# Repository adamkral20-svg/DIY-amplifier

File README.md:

# DIY-amplifier
Custom class-d amplifier board.
I made this since i previously tested a smaller version and i love loud music.
The project uses an oscillator design based on the schematic of [SineLab](https://www.youtube.com/@SineLab). I did change a few things to fit my design better.

This board is a Class - D audio amplifier with analog input(3.5mm audio jack) and gain setting.
It can work with 4-16 ohm speaker on output, and supply voltage < 35V. has OCP latch and a glass fuse.

It uses 4 MOSFETS in an H-bridge configuration, allowing for BTL output and thus higher power from lower supply voltage. 
The main part is the HIP-4081A H-bridge MOSFET gate driver. It can reliably drive the MOSFETS in the hundreds of kHz switching speed.

The onboard discrete oscillator should be around 200kHz.
It uses a pnp constant current source connected to a capacitor, and a MOSFET to discharge the capacitor quickly to generate a Ramp wave.
The MOSFET has 0.7nC gate charge, so the TLV3501 can reliably drive it with its output current capability.

The design by Sine lab

The overcurrent protection shuts off all MOSFETS when triggered, and keeps them off until the button is pressed. 
It uses an npn-pnp SCR based design to output a constant signal with a single pulse.

The pwm modulation is made possible by the MCP6561 comparator. 

To keep voltage levels for the audio and ramp wave similar, I'm using a 2V DC bias on audio, since the ramp wave is 0-4V

The logic circuits are powered by 7812 and 7805 repectively. 
I used many caps between VCC and GND to keep noise low from the H-bridge

# PCB layers
It uses 4 layers, since wiring it up with 2 layers, and still handling enough current was impossible, so i changed it to 4 to fit into < 100mm x 100mm size and handle ~5A on the output.

# Layer 1(Vcc)

# Layer 2(5V)

# Layer 3(12V)

# Layer 4(GND)

# Credits

- [KiCad](https://www.kicad.org/)
- [Fusion 360](https://www.autodesk.com/products/fusion-360/overview)
- [Blueprint project](https://blueprint.hackclub.com/projects/10381)

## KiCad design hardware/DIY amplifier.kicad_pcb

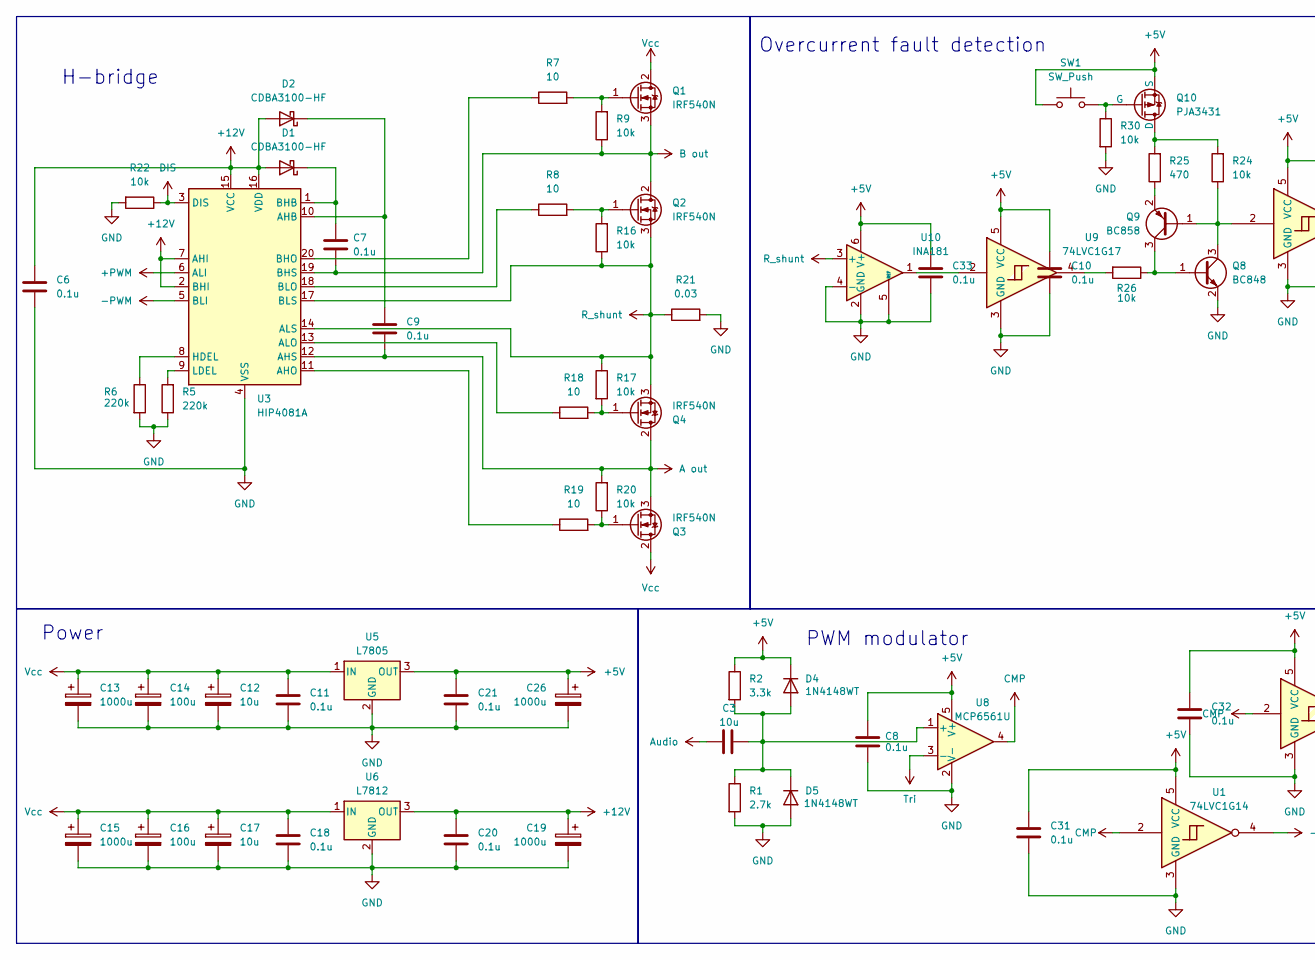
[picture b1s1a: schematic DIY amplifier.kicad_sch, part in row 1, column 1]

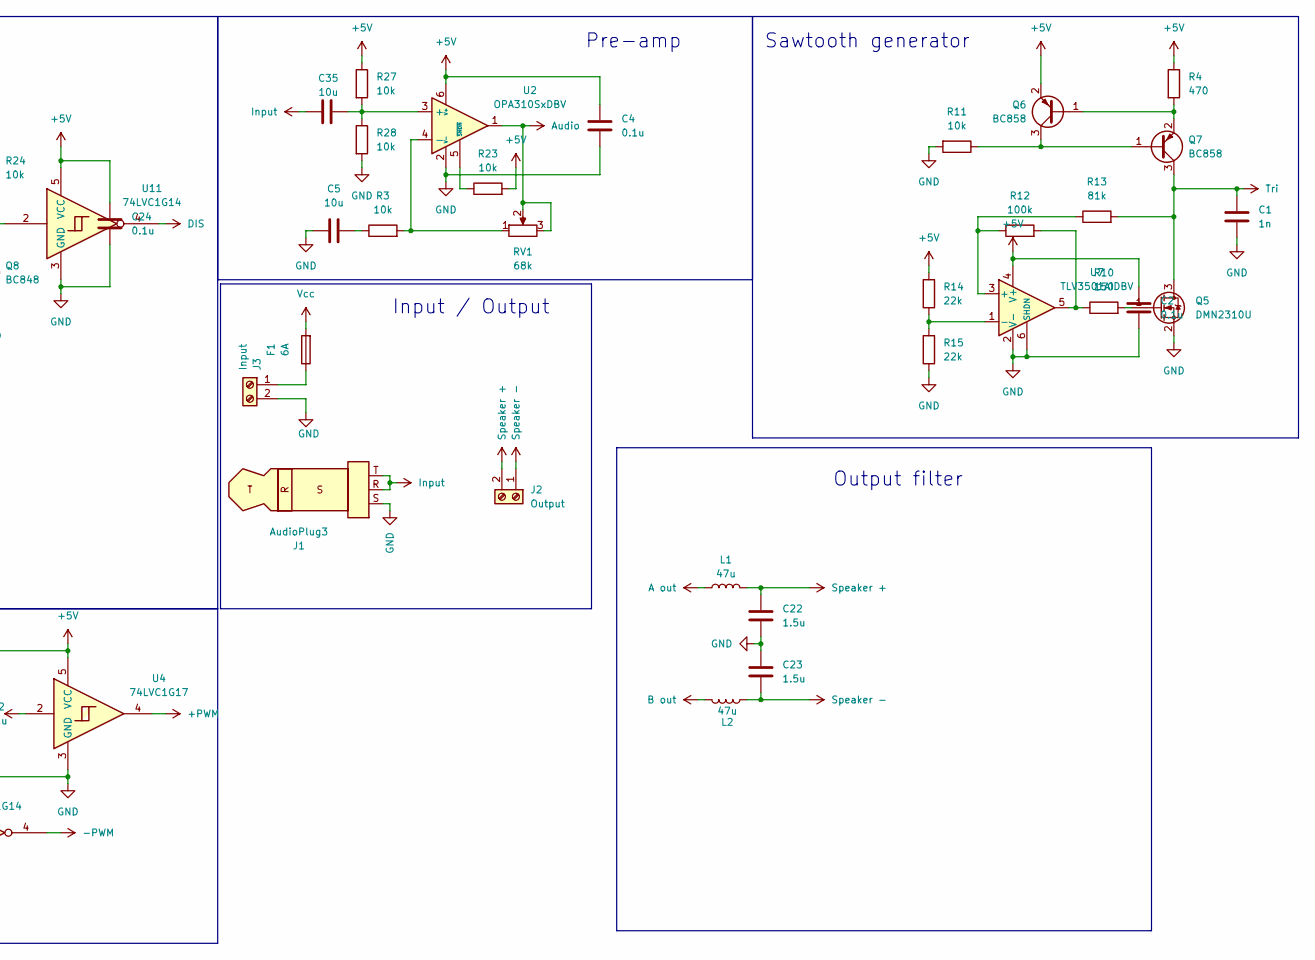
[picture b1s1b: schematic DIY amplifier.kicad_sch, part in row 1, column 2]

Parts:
C1: 1n; C_0402_1005Metric
C2, C4, C6, C7, C8, C9, C10, C24, C31, C32, C33: 0.1u; C_0402_1005Metric
C3, C5, C35: 10u; C_0402_1005Metric
C11, C18, C20, C21: 0.1u; C_Disc_D3.0mm_W1.6mm_P2.50mm
C12, C17: 10u; CP_Radial_D4.0mm_P2.00mm
C13, C15, C19, C26: 1000u; CP_Radial_D12.5mm_P5.00mm
C14, C16: 100u; CP_Radial_D8.0mm_P3.50mm
C22, C23: 1.5u; C_Disc_D3.0mm_W1.6mm_P2.50mm
D1, D2: CDBA3100-HF; D_SMA
D4, D5: 1N4148WT; D_SOD-523
F1: 6A; Fuseholder_Clip-5x20mm_Eaton_1A5601-01_Inline_P20.80x6.76mm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
J1: AudioPlug3; Jack_3.5mm_CUI_SJ-3523-SMT_Horizontal
J2: Output; TerminalBlock_4Ucon_1x02_P3.50mm_Horizontal
J3: Input; TerminalBlock_4Ucon_1x02_P3.50mm_Horizontal
L1, L2: 47u; L_Toroid_Vertical_L14.0mm_W6.3mm_P4.57mm_Pulse_A
Q1, Q2, Q3, Q4: IRF540N; TO-220-3_Horizontal_TabUp
Q5: DMN2310U; SOT-23
Q6, Q7, Q9: BC858; SOT-23
Q8: BC848; SOT-23
Q10: PJA3431; SOT-23-3
R1: 2.7k; R_0603_1608Metric
R2: 3.3k; R_0603_1608Metric
R3, R9, R11, R16, R17, R20, R22, R23, R24, R26, R27, R28, R30: 10k; R_0603_1608Metric
R4, R25: 470; R_0603_1608Metric
R5, R6: 220k; R_0603_1608Metric
R7, R8, R18, R19: 10; R_1206_3216Metric
R10: 150; R_0603_1608Metric
R12: 100k; R_0603_1608Metric
R13: 81k; R_0603_1608Metric
R14, R15: 22k; R_0603_1608Metric
R21: 0.03; R_2512_6332Metric
RV1: 68k; Potentiometer_ACP_CA9-H2,5_Horizontal
SW1: SW_Push; SW_PUSH_6mm_H13mm
U1, U11: 74LVC1G14; SOT-23-5
U2: OPA310SxDBV; SOT-23-6
U3: HIP4081A; DIP-20_W7.62mm
U4, U9: 74LVC1G17; SOT-23-5
U5: L7805; TO-220-3_Vertical
U6: L7812; TO-220-3_Vertical
U7: TLV3501AIDBV; SOT-23-6
U8: MCP6561U; SOT-23-5
U10: INA181; SOT-23-6

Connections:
+5V: C2.1, C4.1, C8.1, C10.1, C21.2, C24.1, C26.1, C31.1, C32.1, C33.1, D4.1 (K), Q6.2 (E), Q10.3 (S), R2.1, R4.1, R14.2, R23.2, R27.1, SW1.1, U1.5 (VCC), U2.6 (V+), U4.5 (VCC), U5.3 (OUT), U7.4 (V+), U8.5 (V+), U9.5 (VCC), U10.6 (V+), U11.5 (VCC)
+12V: C6.1, C19.1, C20.2, D1.2 (A), D2.2 (A), U3.2 (BHI), U3.7 (AHI), U3.15 (VCC), U3.16 (VDD), U6.3 (OUT)
+PWM: U3.6 (ALI), U4.4
-PWM: U1.4, U3.5 (BLI)
A out: C9.2, L1.1, Q3.3 (S), Q4.2 (D), R20.2, U3.12 (AHS)
Audio: C3.1, RV1.2, RV1.3, U2.1
B out: C7.2, L2.1, Q1.3 (S), Q2.2 (D), R9.1, U3.19 (BHS)
CMP: U1.2, U4.2, U8.4
DIS: R22.1, U3.3 (DIS), U11.4
GND: C1.2, C2.2, C4.2, C5.1, C6.2, C8.2, C10.2, C11.1, C12.2, C13.2, C14.2, C15.2, C16.2, C17.2, C18.1, C19.2, C20.1, C21.1, C22.1, C23.1, C24.2, C26.2, C31.2, C32.2, C33.2, D5.2 (A), J1.S, J3.2, Q5.2 (S), Q8.2 (E), R1.2, R5.1, R6.2, R11.2, R15.1, R21.2, R22.2, R28.2, R30.2, U1.3 (GND), U2.2 (V-), U3.4 (VSS), U4.3 (GND), U5.2 (GND), U6.2 (GND), U7.2 (V-), U7.6 (SHDN), U8.2 (V-), U9.3 (GND), U10.2 (GND), U10.4 (-), U10.5 (REF), U11.3 (GND)
Input: C35.1, J1.R, J1.T
unnamed: C5.2, R3.1
unnamed: C7.1, D1.1 (K), U3.1 (BHB)
unnamed: C9.1, D2.1 (K), U3.10 (AHB)
unnamed: C3.2, D4.2 (A), D5.1 (K), R1.1, R2.2, U8.1 (+)
unnamed: F1.1, J3.1
unnamed: Q1.1 (G), R7.2, R9.2
unnamed: Q2.1 (G), R8.2, R16.2
unnamed: Q3.1 (G), R19.2, R20.1
unnamed: Q4.1 (G), R17.2, R18.2
unnamed: Q5.1 (G), R10.2
unnamed: Q6.1 (B), Q7.2 (E), R4.2
unnamed: Q6.3 (C), Q7.1 (B), R11.1
unnamed: Q8.1 (B), Q9.3 (C), R26.1
unnamed: Q8.3 (C), Q9.1 (B), R24.1, U11.2
unnamed: Q9.2 (E), R25.1
unnamed: Q10.1 (D), R24.2, R25.2
unnamed: Q10.2 (G), R30.1, SW1.2
unnamed: R10.1, R12.2, U7.5
unnamed: R26.2, U9.4
unnamed: C35.2, R27.2, R28.1, U2.3 (+)
unnamed: R3.2, RV1.1, U2.4 (-)
unnamed: R23.1, U2.5 (~SHDN)
unnamed: R19.1, U3.11 (AHO)
unnamed: R18.1, U3.13 (ALO)
unnamed: R7.1, U3.20 (BHO)
unnamed: R8.1, U3.18 (BLO)
unnamed: R6.1, U3.8 (HDEL)
unnamed: R5.2, U3.9 (LDEL)
unnamed: R12.1, R13.1, U7.3 (+)
unnamed: R14.1, R15.2, U7.1 (-)
unnamed: U9.2, U10.1
R_shunt: Q2.3 (S), Q4.3 (S), R16.1, R17.1, R21.1, U3.14 (ALS), U3.17 (BLS), U10.3 (+)
Tri: C1.1, Q5.3 (D), Q7.3 (C), R13.2, U8.3 (-)
Vcc: C11.2, C12.1, C13.1, C14.1, C15.1, C16.1, C17.1, C18.2, F1.2, Q1.2 (D), Q3.2 (D), U5.1 (IN), U6.1 (IN)

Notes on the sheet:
H-bridge
Sawtooth generator
Overcurrent fault detection
PWM modulator
Pre-amp
Power
Output filter
Input / Output

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
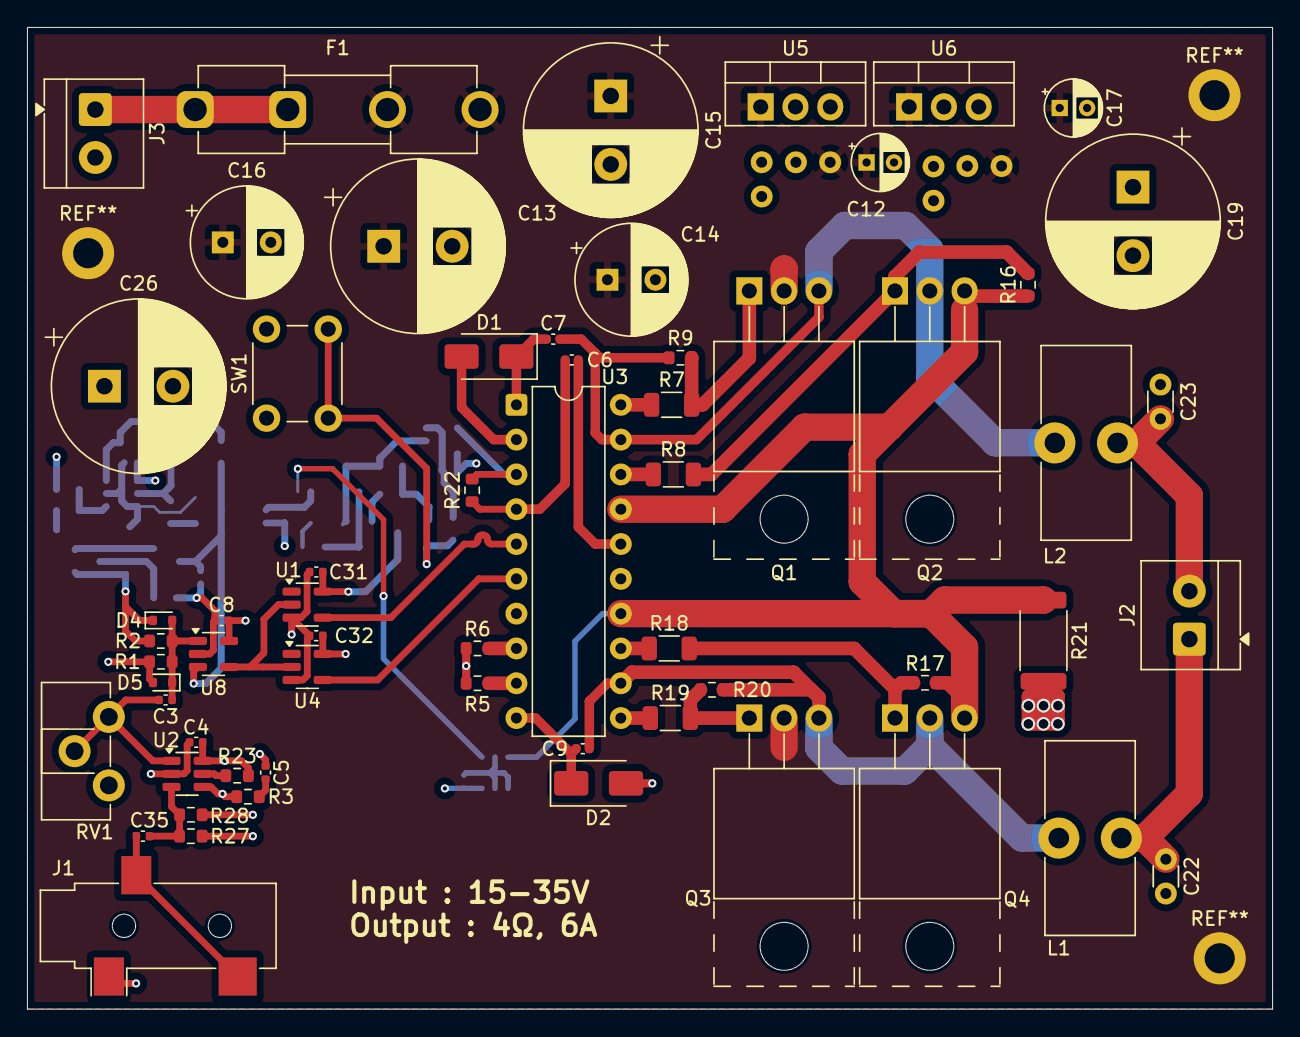
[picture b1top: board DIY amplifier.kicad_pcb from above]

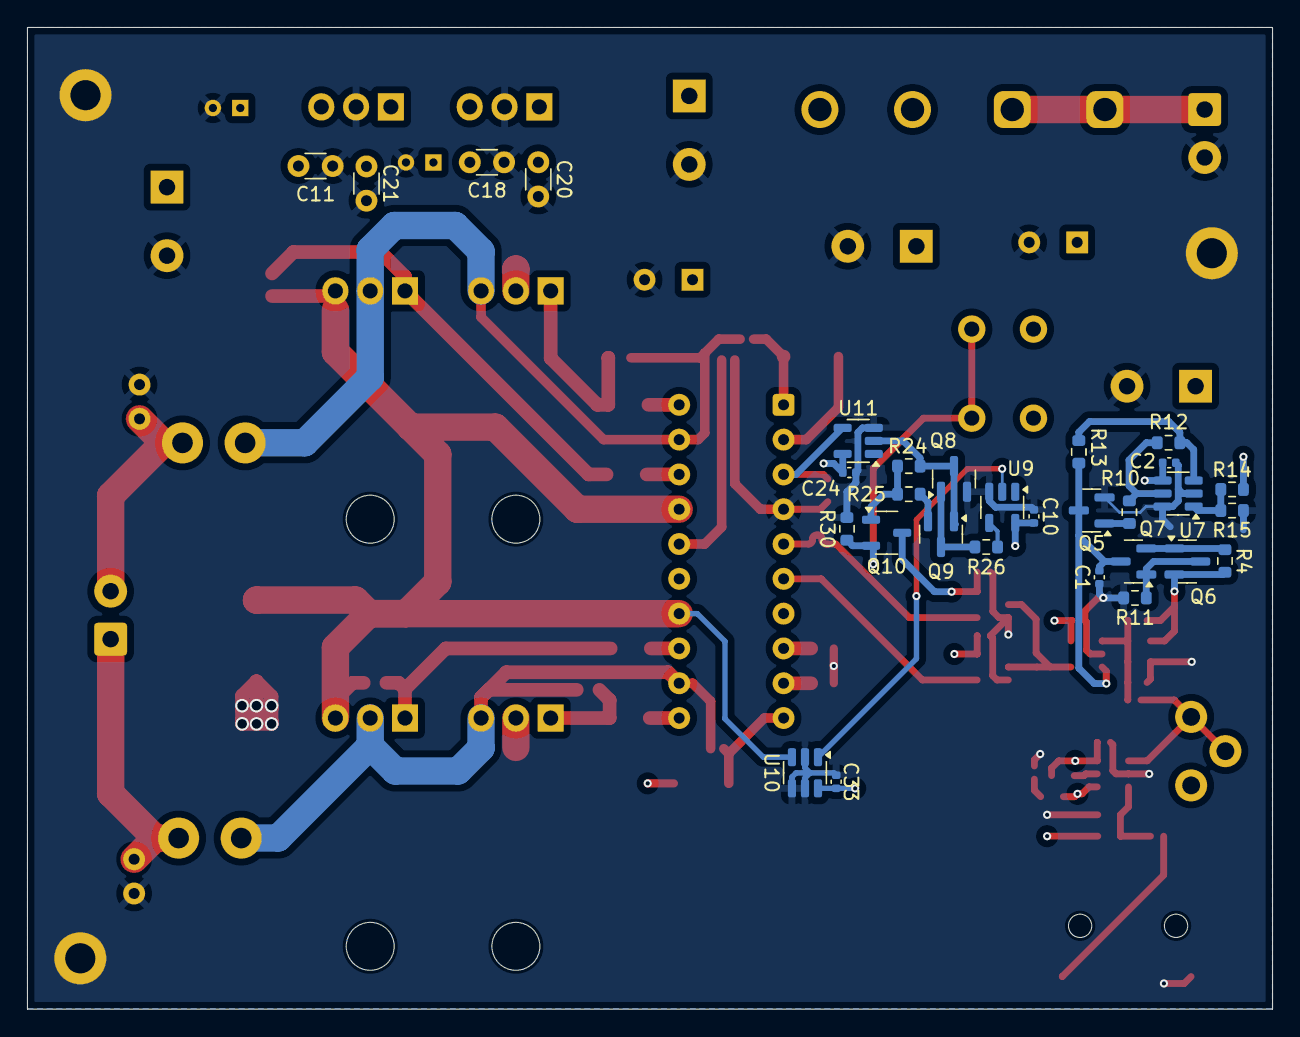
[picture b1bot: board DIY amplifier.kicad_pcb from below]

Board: 4 copper layers, 90.9 x 71.6 mm, 91 parts (30 on the bottom side), 47 nets.

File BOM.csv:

Reference,Value,Footprint,Datasheet,Qty,Part,Price
C1,1n,Capacitor_SMD:C_0402_1005Metric,~,1,DigiKey,"0,10 €"
"C2,C4,C6,C7,C8,C9,C10,C24,C31,C32,C33",0.1u,Capacitor_SMD:C_0402_1005Metric,~,11,DigiKey,"0,02 €"
"C3,C5,C35",10u,Capacitor_SMD:C_0402_1005Metric,~,3,DigiKey,"0,24 €"
"C11,C18,C20,C21",0.1u,Capacitor_THT:C_Disc_D3.0mm_W1.6mm_P2.50mm,~,4,DigiKey,"1,04 €"
"C12,C17",10u,Capacitor_THT:CP_Radial_D4.0mm_P2.00mm,~,2,DigiKey,"0,22 €"
"C13,C15,C19,C26",1000u,Capacitor_THT:CP_Radial_D8.0mm_P2.50mm,~,4,DigiKey,"4,36 €"
"C14,C16",100u,Capacitor_THT:CP_Radial_D6.3mm_P2.50mm,~,2,DigiKey,"0,70 €"
"C22,C23",1.5u,Capacitor_THT:C_Disc_D3.0mm_W1.6mm_P2.50mm,~,2,DigiKey,"1,46 €"
"D1,D2",CDBA3100-HF,Diode_SMD:D_SMA,https://www.comchiptech.com/admin/files/product/CDBA340-HF%2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,2,DigiKey,"1,50 €"
"D4,D5",1N4148WT,Diode_SMD:D_SOD-523,https://www.diodes.com/assets/Datasheets/ds30396.pdf,2,DigiKey,"0,20 €"
F1,6A,Fuse:Fuseholder_Clip-5x20mm_Eaton_1A5601-01_Inline_P20.80x6.76mm_D1.70mm_Horizontal,~,1,DigiKey,"1,70 €"
J1,AudioPlug3,Connector_Audio:Jack_3.5mm_CUI_SJ-3523-SMT_Horizontal,~,1,DigiKey,"0,86 €"
J2,Output,TerminalBlock_4Ucon:TerminalBlock_4Ucon_1x02_P3.50mm_Horizontal,~,1,DigiKey,"0,62 €"
J3,Input,TerminalBlock_4Ucon:TerminalBlock_4Ucon_1x02_P3.50mm_Horizontal,~,1,DigiKey,"0,62 €"
"L1,L2",47u,Inductor_THT:L_Toroid_Vertical_L14.0mm_W6.3mm_P4.57mm_Pulse_A,~,2,Mouser,"3,48 €"
"Q1,Q2,Q3,Q4",IRF540N,Package_TO_SOT_THT:TO-220-3_Horizontal_TabUp,http://www.irf.com/product-info/datasheets/data/irf540n.pdf,4,Mouser,"2,13 €"
Q5,DMN2310U,Package_TO_SOT_SMD:SOT-23,http://www.diodes.com/assets/Datasheets/ds31180.pdf,1,DigiKey,"0,20 €"
"Q6,Q7,Q9",BC858,Package_TO_SOT_SMD:SOT-23,https://www.onsemi.com/pub/Collateral/BC860-D.pdf,3,DigiKey,"0,51 €"
Q8,BC848,Package_TO_SOT_SMD:SOT-23,http://www.infineon.com/dgdl/Infineon-BC847SERIES_BC848SERIE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,1,DigiKey,"0,11 €"
Q10,PJA3431,Package_TO_SOT_SMD:SOT-23-3,https://ngspice.sourceforge.io/docs/ngspice-html-manual/manu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,1,DigiKey,"0,27 €"
R1,2.7k,Resistor_SMD:R_0603_1608Metric,~,1,DigiKey,"0,10 €"
R2,3.3k,Resistor_SMD:R_0603_1608Metric,~,1,DigiKey,"0,10 €"
"R3,R9,R11,R16,R17,R20,R22,R23,R24,R26,R27,R28,R30",10k,Resistor_SMD:R_0603_1608Metric,~,13,DigiKey,"0,39 €"
"R4,R25",470,Resistor_SMD:R_0603_1608Metric,~,2,DigiKey,"0,20 €"
"R5,R6",220k,Resistor_SMD:R_0603_1608Metric,~,2,DigiKey,"0,20 €"
"R7,R8,R18,R19",10,Resistor_SMD:R_1206_3216Metric,~,4,DigiKey,"0,40 €"
R10,150,Resistor_SMD:R_0603_1608Metric,~,1,DigiKey,"0,10 €"
R12,100k,Resistor_SMD:R_0603_1608Metric,~,1,DigiKey,"0,10 €"
R13,81k,Resistor_SMD:R_0603_1608Metric,~,1,DigiKey,"0,10 €"
"R14,R15",22k,Resistor_SMD:R_0603_1608Metric,~,2,DigiKey,"0,20 €"
R21,0.03,Resistor_SMD:R_2512_6332Metric,~,1,DigiKey,"0,55 €"
RV1,68k,"Potentiometer_THT:Potentiometer_ACP_CA9-H2,5_Horizontal",~,1,DigiKey,"2,05 €"
SW1,SW_Push,Button_Switch_THT:SW_PUSH_6mm,~,1,DigiKey,"0,21 €"
"U1,U11",74LVC1G14,Package_TO_SOT_SMD:SOT-23-5,https://www.ti.com/lit/sg/scyt129e/scyt129e.pdf,2,DigiKey,"0,24 €"
U2,OPA310SxDBV,Package_TO_SOT_SMD:SOT-23-6,https://www.ti.com/lit/ds/symlink/opa310.pdf,1,DigiKey,"0,85 €"
U3,HIP4081A,Package_DIP:DIP-20_W7.62mm,http://www.intersil.com/content/dam/Intersil/documents/hip4/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,1,DigiKey,"7,18 €"
"U4,U9",74LVC1G17,Package_TO_SOT_SMD:SOT-23-5,https://www.ti.com/lit/ds/symlink/sn74lvc1g17.pdf,2,DigiKey,"0,30 €"
U5,L7805,Package_TO_SOT_THT:TO-220-3_Vertical,http://www.st.com/content/ccc/resource/technical/document/da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,1,DigiKey,"0,52 €"
U6,L7812,Package_TO_SOT_THT:TO-220-3_Vertical,http://www.st.com/content/ccc/resource/technical/document/da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,1,DigiKey,"0,52 €"
U7,TLV3501AIDBV,Package_TO_SOT_SMD:SOT-23-6,https://www.ti.com/lit/ds/symlink/tlv3501.pdf,1,DigiKey,"3,51 €"
U8,MCP6561U,Package_TO_SOT_SMD:SOT-23-5,http://ww1.microchip.com/downloads/en/DeviceDoc/MCP6561-1R-1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,1,DigiKey,"0,55 €"
U10,INA181,Package_TO_SOT_SMD:SOT-23-6,http://www.ti.com/lit/ds/symlink/ina181.pdf,1,DigiKey,"0,43 €"
,,,,,,"39,14 €"

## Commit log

2026-01-26 Rename folder for DIY amplifier PCB
2026-01-30 Create tml
2026-01-30 Enhance README with detailed amplifier specifications
    Expanded the README with detailed descriptions of the Class-D amplifier features, including specifications, design improvements, and component functionalities.
2026-01-30 Enhance README with personal notes and input details
    Added personal motivation for creating the amplifier and clarified the input type.
2026-01-30 Enhance README with PCB layers and credits
    Added PCB layer details and credits section to README.
2026-01-30 Enhance README with oscillator design information
    Added details about the oscillator design and included images.
2026-01-30 Fix formatting and remove extra line in README
    Removed an extra line and adjusted formatting in the README.
